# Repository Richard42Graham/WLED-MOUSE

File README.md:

# WLED-Mouse

*Note: PCB is still very much work in progress*

PCB files for a for ESP32 board that can attach an INMP441 or ICS-43434 I²S microphone. It is intended to use together with [SR-WLED](https://github.com/atuline/WLED/) for mixing sound reactive and addressable LEDs together.

## I2S Digital Microphone information
The INMP441 is an omnidirectional digital microphone which communicates via I²S. It can be bought from a number of places, for example [Aliexpress](https://www.aliexpress.com/i/32962426410.html).

### Microphone hookup

Hookup instructions is taken from the [SR-WLED wiki](https://github.com/atuline/WLED/wiki/Digital-Microphone-Hookup#i2s-digital-audio).
| from INMP441, ICS-43434 | to ESP32 GPIO | |
| ---   | ---   | --- |
| L/R   | Gnd   | ground => left channel. Don't leave this pin unconnected!
| SD    | 32    | serial data
| WS    | 15    | left right clock
| SCK   | 14    | serial clock
| VDD   | 3.3V  | power don't use 5V!
| GND   | Gnd   | ground, 0V

## WLED setup

1. Fetch the binary from [SR-WLED](https://github.com/atuline/WLED/releases/latest) and flash to ESP32 board
1. Boot up WLED device and go to the "Sound setting" menu
2. Select `Generic I2S`
3. Reboot device
4. Have fun with sound reactive LEDs

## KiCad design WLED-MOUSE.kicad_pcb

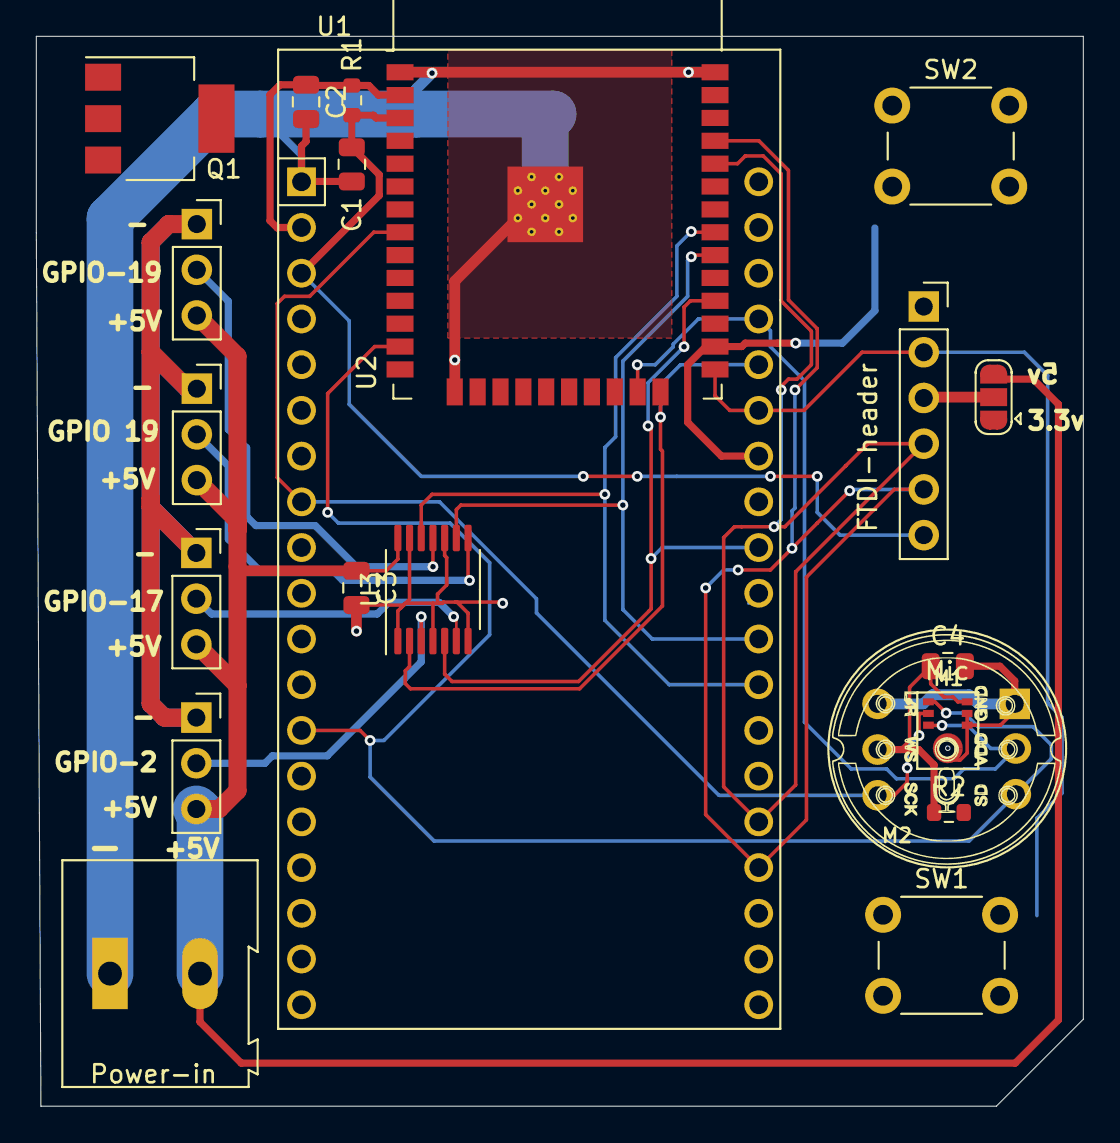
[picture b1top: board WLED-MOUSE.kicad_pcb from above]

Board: 4 copper layers, 58.2 x 59.4 mm, 21 parts (0 on the bottom side), 22 nets.

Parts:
C1, C3, C4: C; C_0805_2012Metric
C2: 25uF; C_0805_2012Metric
J1: FTDI-header; PinSocket_1x06_P2.54mm_Vertical
J2: Power-in; TerminalBlock_Altech_AK300-2_P5.00mm
J4, J6, J7, J8: Pixel-strip; PinSocket_1x03_P2.54mm_Vertical
JP1: SolderJumper_3_Bridged12; SolderJumper-3_P1.3mm_Open_RoundedPad1.0x1.5mm
M1: INMP441; MIC_DMM-4026-B-I2S-R
M2: INMP441-TH; MIC_DMM-4026-B-I2S-R-TH
Q1: NDT3055L; SOT-223-3_TabPin2
R1, R2: R; R_0603_1608Metric
SW1, SW2: SW_MEC_5E; SW_PUSH_6mm
U1: ESP32-WROOM-32D; ESP32-DEVKITC-32D
U2: ESP32-WROOM-32D; ESP32-WROOM-32
U3: SN74LV4T125; TSSOP-14_4.4x5mm_P0.65mm

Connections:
+3.3V: C2.1, C4.1, JP1.1 (A), M1.7 (Vcc), M2.5 (Vcc), R1.1, R2.1, U1.2 (VDD), U2.2 (VDD)
+5V: C3.1, J2.2, J4.3, J6.3, J7.3, J8.3, JP1.3 (B), U3.14 (VCC)
/Button: SW2.1, U1.26 (IO4), U2.26 (IO4)
/GPIO-0: J1.2, SW1.1, U1.25 (IO0), U2.25 (IO0)
/LED-1: U1.24 (IO2), U2.24 (IO2), U3.2
/LED-2: U1.28 (IO17), U2.28 (IO17), U3.5
/LED-3: U1.30 (IO18), U2.30 (IO18), U3.9
/LED-4: U1.31 (IO19), U2.31 (IO19), U3.12
/Power Relay Pin: Q1.1 (G), U1.29 (IO5), U2.29 (IO5)
/Reset: C1.1, J1.6, R1.2, U1.3 (EN), U2.3 (EN)
/Rx: J1.4, U1.34 (RXD0/IO3), U2.34 (RXD0/IO3)
/SCK: M1.1 (SCK), M2.3 (SCK), U1.13 (IO14), U2.13 (IO14)
/SD: M1.2 (SD), M2.6 (SD), U1.8 (IO32), U2.8 (IO32)
/Tx: J1.5, U1.35 (TXD0/IO1), U2.35 (TXD0/IO1)
/WS: M1.3 (WS), M2.2 (WS), U1.23 (IO15), U2.23 (IO15)
GND: C1.2, C2.2, C3.2, C4.2, J1.1, J2.1, M1.4 (L/R), M1.5 (GND), M1.6 (GND), M2.1 (L/R), M2.4 (GND), Q1.3 (S), SW1.2, SW2.2, U1.1 (GND), U1.15 (GND), U1.38 (GND), U2.1 (GND), U2.15 (GND), U2.38 (GND), U2.39 (GND), U3.1, U3.4, U3.7 (GND), U3.10, U3.13
unnamed: J1.3, JP1.2 (C)
unnamed: J4.1, J6.1, J7.1, J8.1, Q1.2 (D)
unnamed: J4.2, U3.3
unnamed: J6.2, U3.6
unnamed: J7.2, U3.8
unnamed: J8.2, U3.11

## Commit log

2023-03-10 initial commit on WLED-MOUSE (a sound reactive WLED kit for labitat)
2023-03-15 add MIT license
2023-03-15 README: add basic project details and hookup information
2023-03-15 minor readability improvements
2023-03-16 added some parts, symbols and fooprints for a few things. allso 'touched grass' as this was recomended by a frined who said i was working too hard in linux. :3
2023-03-26 added some footprints for components
2023-04-04 added some more nice little bits
2023-04-06 wired up the schimatic for the level shifters.
2023-04-06 added the JLC PCB rules and settings, for eventual prodcution, also tried to add some of the stuff for the mic.
2023-04-14 added footprint for the thought hole mic board, thing?
2023-04-27 started doing some more layout
2023-05-01 checking its up to date,
2023-06-16 started some routing and layout stuff
2023-08-28 added GPIO names, to silk screen, to make life easier when using the board.
